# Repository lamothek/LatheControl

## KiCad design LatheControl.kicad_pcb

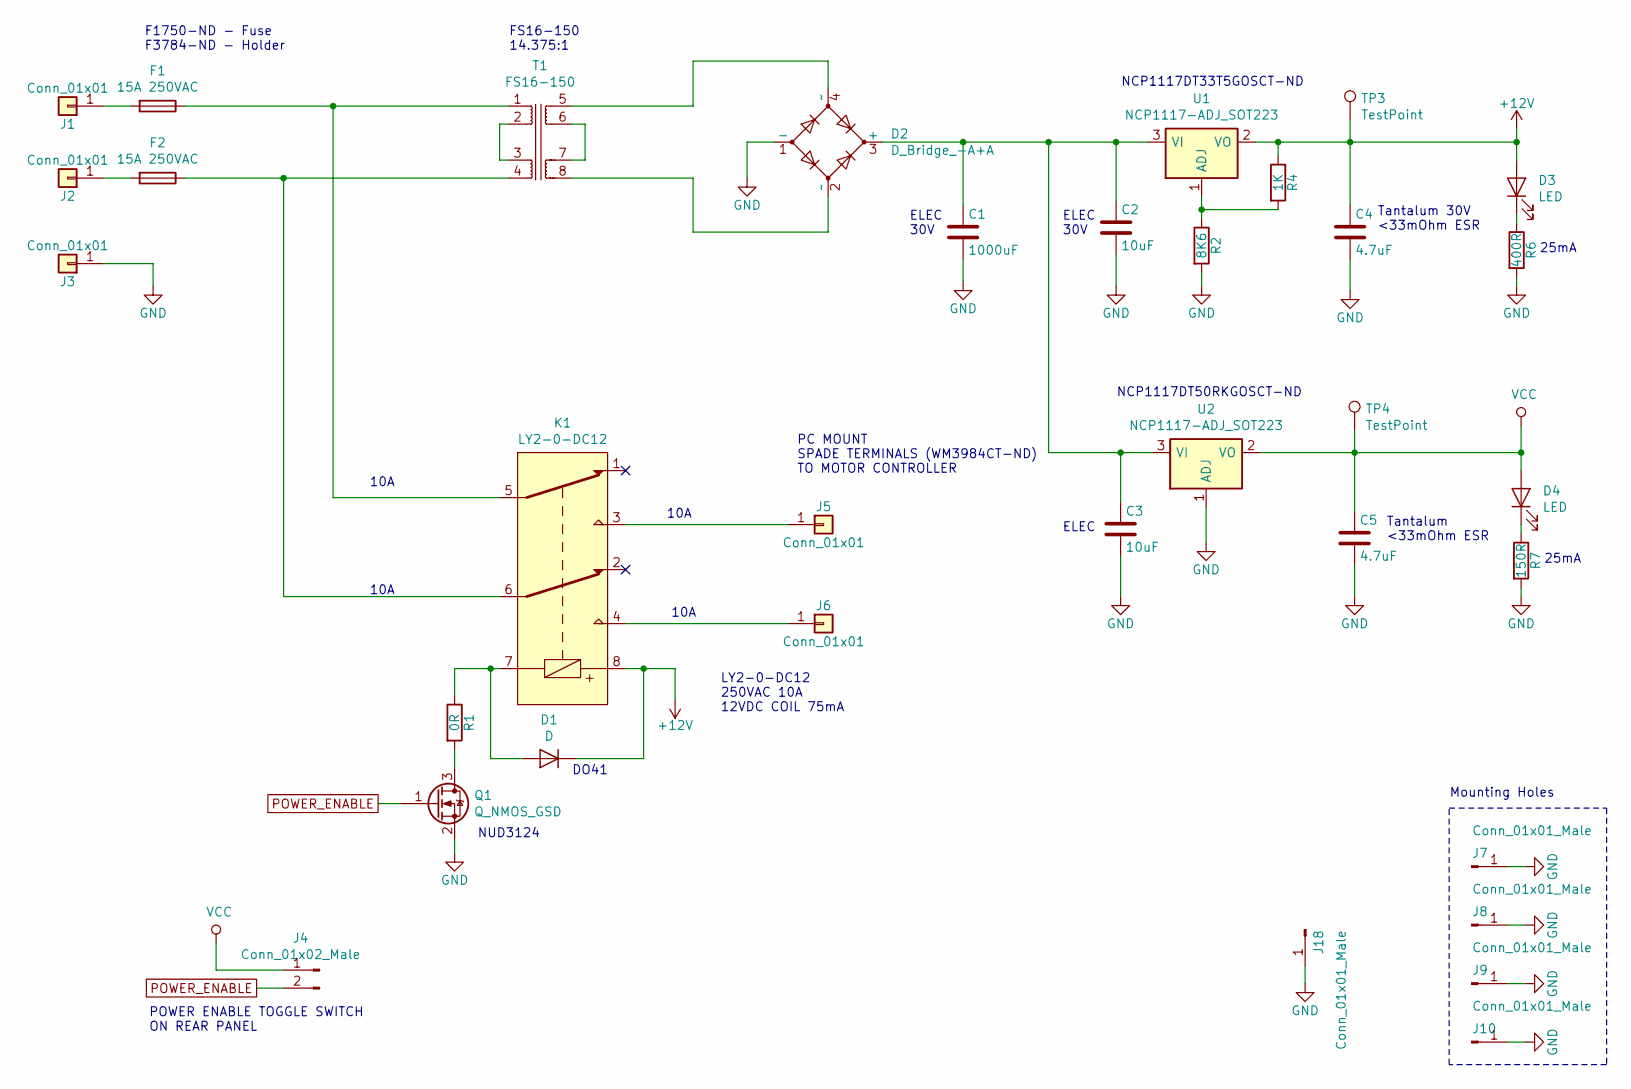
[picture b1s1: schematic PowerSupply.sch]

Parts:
C1: 1000uF; CP_Radial_D10.0mm_P5.00mm
C2, C3: 10uF; CP_Elec_4x4.5
C4: 4.7uF; CP_Tantalum_Case-C_EIA-6032-28_Hand
C5: 4.7uF; CP_Tantalum_Case-A_EIA-3216-18_Hand
D1: D; D_DO-41_SOD81_P10.16mm_Horizontal
D2: D_Bridge_-A+A; Diode_Bridge_18.5x5.5
D3, D4: LED; LED_0805_HandSoldering
F1, F2: 15A 250VAC; 100056Z
J1, J2, J3, J5, J6: Conn_01x01; 0197054203
J4: Conn_01x02_Male; JST_EH_B02B-EH-A_02x2.50mm_Straight
J7, J8, J9, J10: Conn_01x01_Male; MountingHole_3.2mm_M3_Pad_Via
J18: Conn_01x01_Male; 0197054203
K1: LY2-0-DC12; PT08-0
Q1: Q_NMOS_GSD; SOT-23W_Handsoldering
R1: 0R; R_0603_HandSoldering
R2: 8K6; R_0603_HandSoldering
R4: 1K; R_0603_HandSoldering
R6: 400R; R_0603_HandSoldering
R7: 150R; R_0603_HandSoldering
T1: FS16-150
TP3, TP4: TestPoint; Test_Point_Keystone_5019_Minature
U1, U2: NCP1117-ADJ_SOT223; TO-252-3_TabPin2

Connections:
+12V: C4.1, D1.1 (K), D3.2 (A), K1.8, R4.1, TP3.1, U1.2 (VO); also elsewhere on the board
GND: C1.2, C2.2, C3.2, C4.2, C5.2, D2.1 (-), J3.1, J7.1, J8.1, J9.1, J10.1, J18.1, Q1.2 (S), R2.2, R6.2, R7.2, U2.1 (ADJ); also elsewhere on the board
unnamed: C1.1, C2.1, C3.1, D2.3 (+), U1.3 (VI), U2.3 (VI)
unnamed: D1.2 (A), K1.7, R1.1
unnamed: D2.2 (~~), T1.8
unnamed: D2.4 (~~), T1.5
unnamed: D3.1 (K), R6.1
unnamed: D4.1 (K), R7.1
unnamed: F1.1, K1.5, T1.1
unnamed: F1.2, J1.1
unnamed: F2.1, K1.6, T1.4
unnamed: F2.2, J2.1
unnamed: J5.1, K1.3
unnamed: J6.1, K1.4
unnamed: Q1.3 (D), R1.2
unnamed: R2.1, R4.2, U1.1 (ADJ)
unnamed: T1.2, T1.3
unnamed: T1.6, T1.7
POWER_ENABLE: J4.2, Q1.1 (G)
VCC: C5.1, D4.2 (A), J4.1, TP4.1, U2.2 (VO); also elsewhere on the board

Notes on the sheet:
Tantalum 30V <33mOhm ESR
Tantalum <33mOhm ESR
ELEC
ELEC 30V
PC MOUNT SPADE TERMINALS (WM3984CT-ND) TO MOTOR CONTROLLER
NUD3124
POWER ENABLE TOGGLE SWITCH ON REAR PANEL
10A
25mA
LY2-0-DC12 250VAC 10A 12VDC COIL 75mA
FS16-150 14.375:1
DO41
NCP1117DT50RKGOSCT-ND
NCP1117DT33T5GOSCT-ND
F1750-ND - Fuse F3784-ND - Holder
Mounting Holes

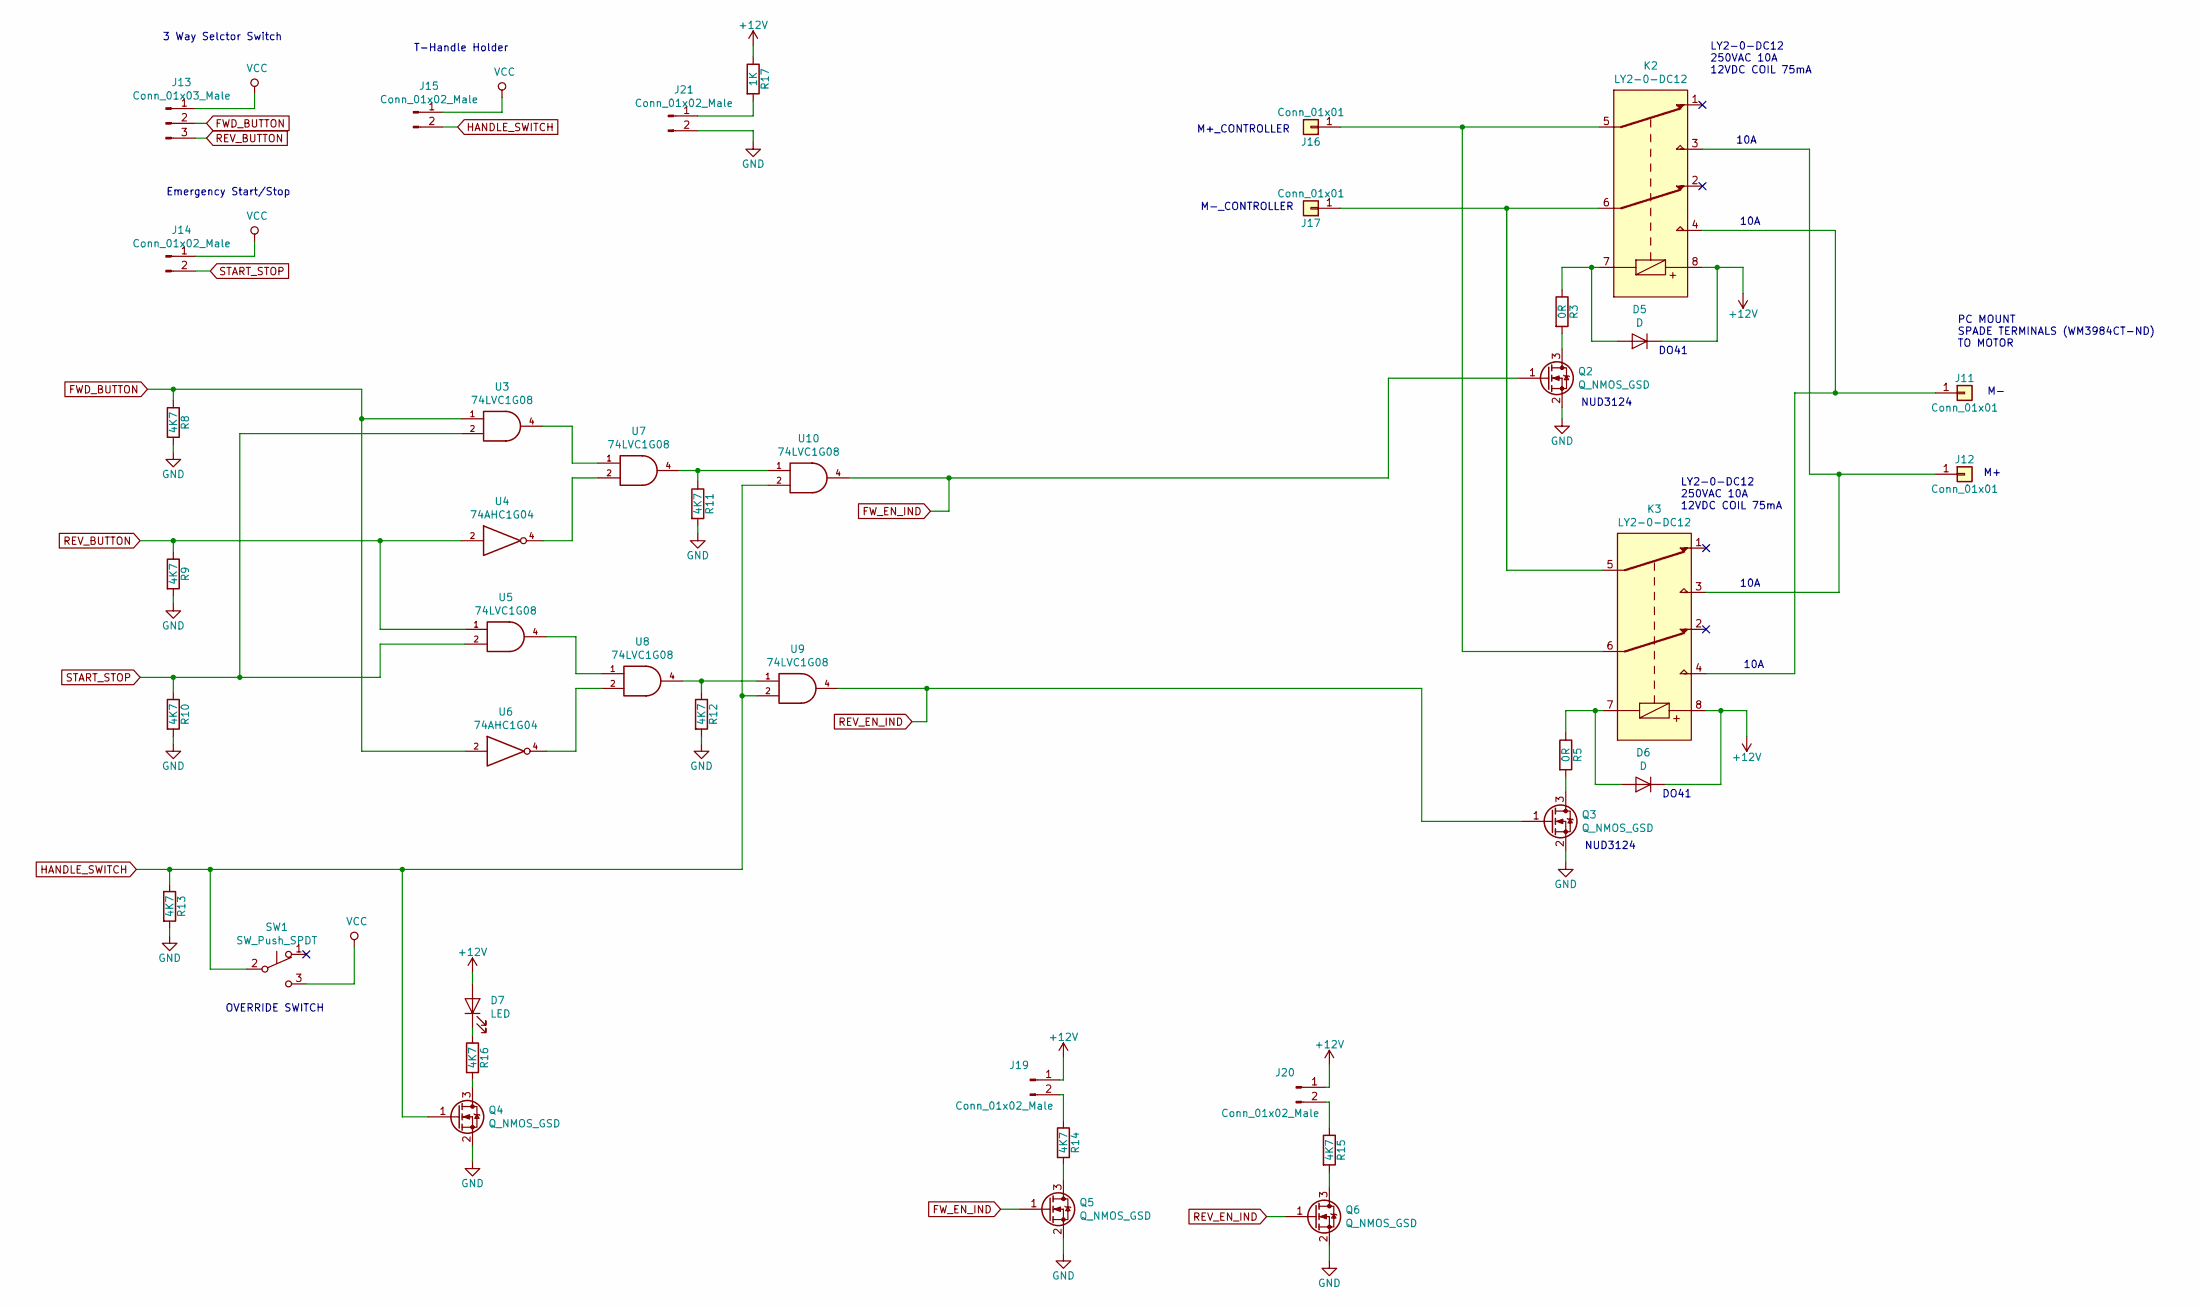
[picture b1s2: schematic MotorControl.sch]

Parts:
D5, D6: D; D_DO-41_SOD81_P10.16mm_Horizontal
D7: LED; LED_0805_HandSoldering
J11, J12, J16, J17: Conn_01x01; 0197054203
J13: Conn_01x03_Male; JST_EH_B03B-EH-A_03x2.50mm_Straight
J14, J15, J19, J20, J21: Conn_01x02_Male; JST_EH_B02B-EH-A_02x2.50mm_Straight
K2, K3: LY2-0-DC12; PT08-0
Q2, Q3, Q4, Q5, Q6: Q_NMOS_GSD; SOT-23W_Handsoldering
R3, R5: 0R; R_0603_HandSoldering
R8, R9, R10, R11, R12, R13, R14, R15, R16: 4K7; R_0603_HandSoldering
R17: 1K; R_0603_HandSoldering
SW1: SW_Push_SPDT; SW_CuK_OS102011MA1QN1_SPDT_Angled
U3, U5, U7, U8, U9, U10: 74LVC1G08; SOT-23-5_HandSoldering
U4, U6: 74AHC1G04; SOT-23-5_HandSoldering

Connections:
+12V: D5.1 (K), D6.1 (K), D7.2 (A), J19.1, J20.1, K2.8, K3.8, R17.1; also elsewhere on the board
FWD_BUTTON: J13.2, R8.1, U3.1, U6.2
FW_EN_IND: Q2.1 (G), Q5.1 (G), U10.4
GND: J21.2, Q2.2 (S), Q3.2 (S), Q4.2 (S), Q5.2 (S), Q6.2 (S), R8.2, R9.2, R10.2, R11.2, R12.2, R13.2, U3.3 (GND), U4.3 (GND), U5.3 (GND), U6.3 (GND), U7.3 (GND), U8.3 (GND), U9.3 (GND), U10.3 (GND); also elsewhere on the board
HANDLE_SWITCH: J15.2, Q4.1 (G), R13.1, SW1.2 (B), U9.2, U10.2
unnamed: D5.2 (A), K2.7, R3.1
unnamed: D6.2 (A), K3.7, R5.1
unnamed: D7.1 (K), R16.1
unnamed: J11.1, K2.4, K3.4
unnamed: J12.1, K2.3, K3.3
unnamed: J16.1, K2.5, K3.6
unnamed: J17.1, K2.6, K3.5
unnamed: J19.2, R14.1
unnamed: J20.2, R15.1
unnamed: J21.1, R17.2
unnamed: Q2.3 (D), R3.2
unnamed: Q3.3 (D), R5.2
unnamed: Q4.3 (D), R16.2
unnamed: Q5.3 (D), R14.2
unnamed: Q6.3 (D), R15.2
unnamed: R11.1, U7.4, U10.1
unnamed: R12.1, U8.4, U9.1
unnamed: U3.4, U7.1
unnamed: U4.4, U7.2
unnamed: U5.4, U8.1
unnamed: U6.4, U8.2
REV_BUTTON: J13.3, R9.1, U4.2, U5.1
REV_EN_IND: Q3.1 (G), Q6.1 (G), U9.4
START_STOP: J14.2, R10.1, U3.2, U5.2
VCC: J13.1, J14.1, J15.1, SW1.3 (C), U3.5 (VCC), U4.5 (VCC), U5.5 (VCC), U6.5 (VCC), U7.5 (VCC), U8.5 (VCC), U9.5 (VCC), U10.5 (VCC); also elsewhere on the board

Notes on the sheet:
PC MOUNT SPADE TERMINALS (WM3984CT-ND) TO MOTOR
NUD3124
10A
LY2-0-DC12 250VAC 10A 12VDC COIL 75mA
DO41
3 Way Selctor Switch
Emergency Start/Stop
M+_CONTROLLER
M-_CONTROLLER
T-Handle Holder
OVERRIDE SWITCH

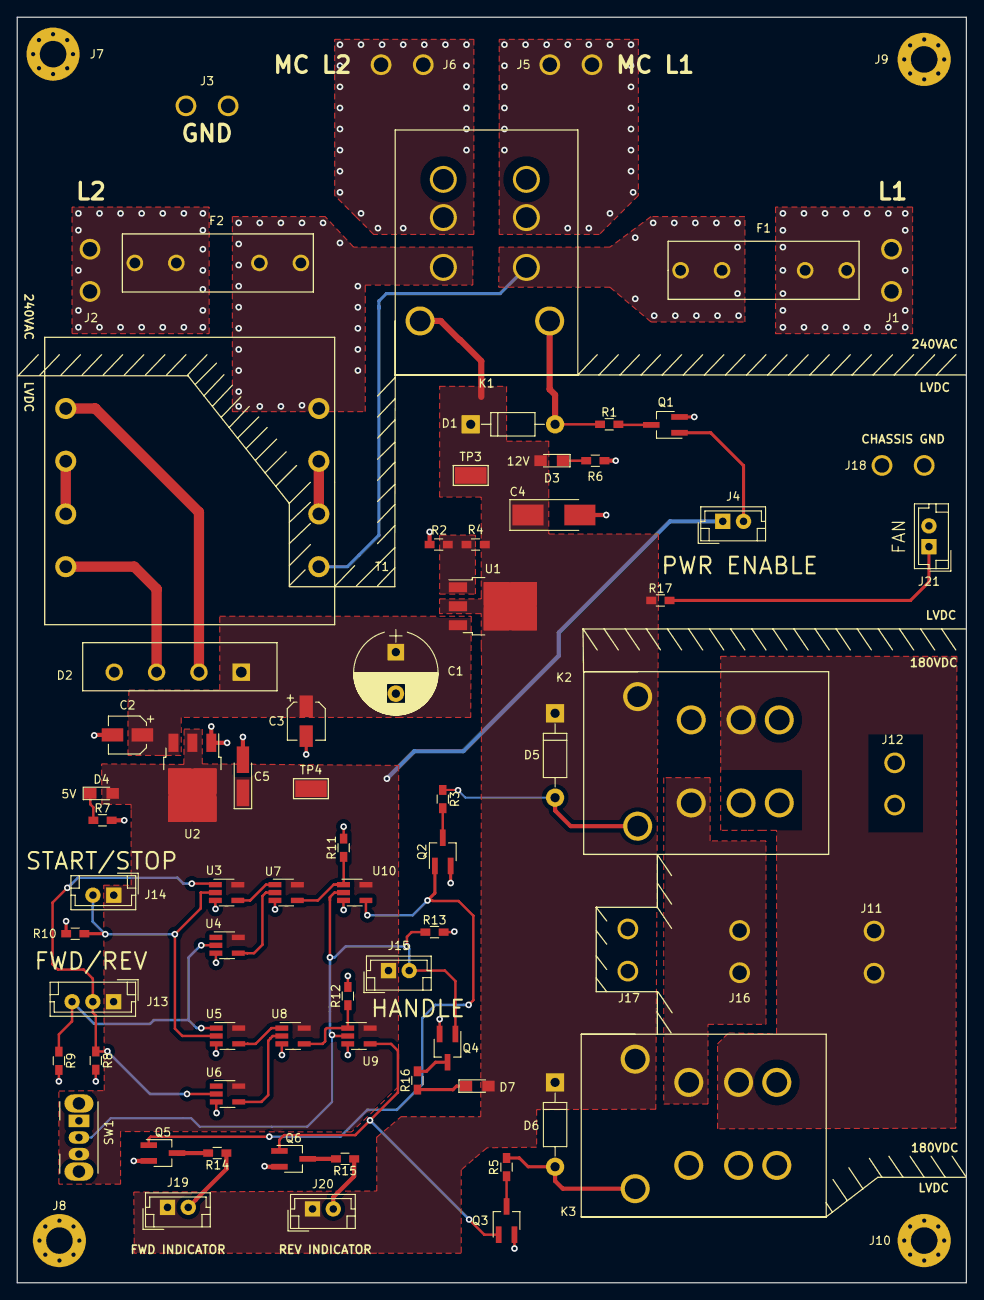
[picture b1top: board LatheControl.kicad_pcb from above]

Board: 2 copper layers, 114.3 x 152.4 mm, 75 parts (0 on the bottom side), 47 nets.

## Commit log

2019-06-15 Initial commit. Schematic, pcb, bom in review stage.
2020-03-26 Output gerber files sent to pcbway for manufacture.
2020-03-26 Schematic, board and project files updated with final design notes and board completion. Added part to customFootprints.
2020-03-26 PDF files for top and bottom views of pcb output and system schematic.
